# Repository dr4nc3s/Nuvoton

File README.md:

<h1>Nuvoton Main Folder</h1>

Found some Nuvoton MCUs at a 90% discount for a sample sale (max 5pcs/chip) and bought 8 different chips. I need to make breakout/eval boards for them, so I'll use this as an opportunity to learn how to use KiCad (normally use Eagle) and learn developing with uKeil.

<h2> Chips Bought </h2>
1. **M0519SD3AE** - Cortex M0, 64KB Flash, LQFP64_7mmx7mm
	1. UART x2, SPI x2, I2C x1, LIN x2
	2. 16KB RAM, 4KB data flash
	3. Timer x4
	4. PWM x10,
	5. ADC 16-channel, OA x2, Comparator x2

2. **NUC505DS13Y** - Cortex M4, 2048KB Flash, LQFP64
	1. UART x3, USB
	2. I2C x2, I2S x1, SPI x3, SD Host x1
	3. PWM x4, ADC (12-bit) x8
	4. 24-bit Audio CODEC & supports Headphone Out
	5. Digital Mic
	6. RTC, Timer x4
	7. 128KB SRAM
	8. 8KB ISP Loader ROM 

3. **M482SIDAE** - Cortex M4, 512KB Flash, LQFP64_7mmx7mm
	1. UART x6
	2. I2C x3, I2S x1, SPI x4
	3. PWM (16-bit) x24, ADC (12-bit) x16, DAC (12-bit) x2
	4. LIN x2
	5. RTC, Timer x4
	6. 160KB SRAM
	7. 4KB ISP Loader ROM 
	8. LCD Parallel Data Bus, 16-lines

4. **M451VE6AE** - Cortex M4, 128KB Flash, LQFP100
	1. UART x4 + 1 (1 full-duplex)
	2. I2C x2, I2S x2, SPI x3
	3. PWM x12, ADC (12-bit) x16, DAC (12-bit)
	4. LIN x2
	5. RTC, Timer x4
	6. 32KB SRAM
	7. 4KB ISP Loader ROM

5. **M452RE6AE** - Cortex M4, 128KB Flash, LQFP64
	1. UART x4 + 1 (1 full-duplex)
	2. I2C x2, I2S x2, SPI x3
	3. PWM x12, ADC (12-bit) x16, DAC (12-bit)
	4. LIN x2
	5. RTC, Timer x4
	6. 32KB SRAM
	7. 4KB ISP Loader ROM 

6. **NUC505YO13Y** - Cortex M4, 2048KB Flash, QFN88
	1. UART x3, USB
	2. I2C x2, I2S x1, SPI x3, SD Host x1
	3. PWM x4, ADC (12-bit) x8
	4. 24-bit Audio CODEC
	5. Digital Mic
	6. RTC, Timer x4
	7. 128KB SRAM
	8. 8KB ISP Loader ROM

7. **NUC442RI8AE** - Cortex M4, 512KB Flash, LQFP64
	1. UART x4 + 3 (3 full-duplex)
	2. I2C x2, I2S x1, SPI x3
	3. PWM x8, ADC (12-bit) x8, DAC
	4. LIN x4
	5. USB
	6. RTC, Timer x4
	7. 64KB SRAM
	8. 16KB ISP Loader ROM

8. **M451VG6AE** - Cortex M4, 256KB Flash, LQFP100
	1. UART x4 + 1 (1 full-duplex)
	2. I2C x2, I2S x2, SPI x3
	3. PWM x12, ADC (12-bit) x16, DAC (12-bit)
	4. LIN x2
	5. RTC, Timer x4
	6. 32KB SRAM
	7. 4KB ISP Loader ROM

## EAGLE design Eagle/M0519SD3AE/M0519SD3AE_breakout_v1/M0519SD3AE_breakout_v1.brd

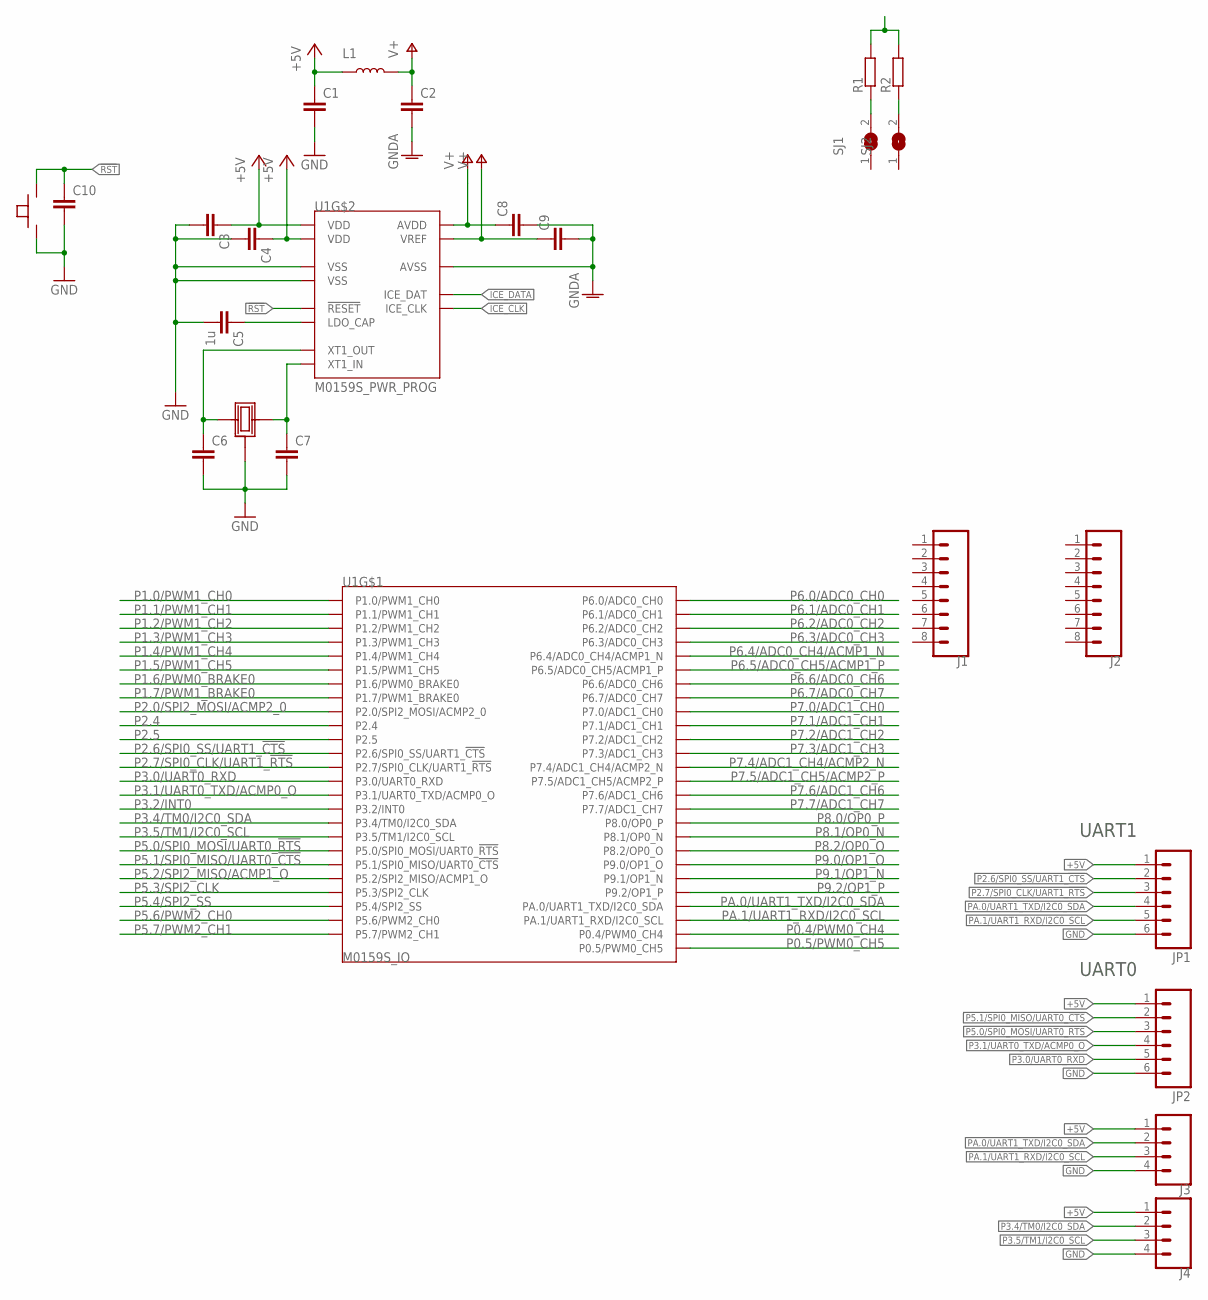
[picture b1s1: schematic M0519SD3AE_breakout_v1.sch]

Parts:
C1, C2, C3, C4, C6, C7, C8, C9, C10: CAP0603-CAP; 0603-CAP
C5: 1u; 0603-CAP
J1, J2: M08; 1X08
J3, J4: M04; 1X04
JP1, JP2: M06LOCK; 1X06_LOCK
L1: INDUCTOR_FB; 0603-FB
R1, R2: RESISTOR0603-RES; 0603-RES
SJ1, SJ2: SJ
U1: M0159S; LQFP-64_7MMX7MMX1.6MM
U$1: CRYSTAL_EPSON; TSX3225
U$2: 95C06B2GWRT; PUSH-BUTTON-95C06B2GWRT

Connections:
!RST: C10.1, U1.60 (!RESET), U$2.P3 (B), U$2.P4 (B)
+5V: C1.1, C3.1, C4.1, J3.1, J4.1, JP1.1, JP2.1, L1.1, U1.6 (VDD), U1.21 (VDD)
GND: C1.2, C3.2, C4.2, C5.2, C6.2, C7.2, C10.2, J3.4, J4.4, JP1.6, JP2.6, U1.7 (VSS), U1.22 (VSS), U$1.2, U$1.4 (2), U$2.P1 (A), U$2.P2 (A)
GNDA: C2.2, C8.2, C9.2, U1.46 (AVSS)
ICE_CLK: U1.64 (ICE_CLK)
ICE_DATA: U1.63 (ICE_DAT)
unnamed: R1.1, SJ1.2
unnamed: C5.1, U1.5 (LDO_CAP)
unnamed: C7.1, U1.62 (XT1_IN), U$1.1
unnamed: C6.1, U1.61 (XT1_OUT), U$1.3
unnamed: R2.1, SJ2.2
unnamed: R1.2, R2.2
P0.4/PWM0_CH4: U1.30 (P0.4/PWM0_CH4)
P0.5/PWM0_CH5: U1.29 (P0.5/PWM0_CH5)
P1.0/PWM1_CH0: U1.18 (P1.0/PWM1_CH0)
P1.1/PWM1_CH1: U1.17 (P1.1/PWM1_CH1)
P1.2/PWM1_CH2: U1.16 (P1.2/PWM1_CH2)
P1.3/PWM1_CH3: U1.15 (P1.3/PWM1_CH3)
P1.4/PWM1_CH4: U1.14 (P1.4/PWM1_CH4)
P1.5/PWM1_CH5: U1.13 (P1.5/PWM1_CH5)
P1.6/PWM0_BRAKE0: U1.12 (P1.6/PWM0_BRAKE0)
P1.7/PWM1_BRAKE0: U1.4 (P1.7/PWM1_BRAKE0)
P2.0/SPI2_MOSI/ACMP2_0: U1.31 (P2.0/SPI2_MOSI/ACMP2_0)
P2.4: U1.28 (P2.4)
P2.5: U1.27 (P2.5)
P2.6/SPI0_SS/UART1_!CTS: JP1.2, U1.26 (P2.6/SPI0_SS/UART1_!CTS)
P2.7/SPI0_CLK/UART1_!RTS: JP1.3, U1.25 (P2.7/SPI0_CLK/UART1_!RTS)
P3.0/UART0_RXD: JP2.5, U1.19 (P3.0/UART0_RXD)
P3.1/UART0_TXD/ACMP0_O: JP2.4, U1.20 (P3.1/UART0_TXD/ACMP0_O)
P3.2/INT0: U1.3 (P3.2/INT0)
P3.4/TM0/I2C0_SDA: J4.2, U1.2 (P3.4/TM0/I2C0_SDA)
P3.5/TM1/I2C0_SCL: J4.3, U1.1 (P3.5/TM1/I2C0_SCL)
P5.0/SPI0_MOSI/UART0_!RTS: JP2.3, U1.23 (P5.0/SPI0_MOSI/UART0_!RTS)
P5.1/SPI0_MISO/UART0_!CTS: JP2.2, U1.24 (P5.1/SPI0_MISO/UART0_!CTS)
P5.2/SPI2_MISO/ACMP1_O: U1.32 (P5.2/SPI2_MISO/ACMP1_O)
P5.3/SPI2_CLK: U1.33 (P5.3/SPI2_CLK)
P5.4/SPI2_SS: U1.34 (P5.4/SPI2_SS)
P5.6/PWM2_CH0: U1.11 (P5.6/PWM2_CH0)
P5.7/PWM2_CH1: U1.10 (P5.7/PWM2_CH1)
P6.0/ADC0_CH0: U1.42 (P6.0/ADC0_CH0)
P6.1/ADC0_CH1: U1.41 (P6.1/ADC0_CH1)
P6.2/ADC0_CH2: U1.40 (P6.2/ADC0_CH2)
P6.3/ADC0_CH3: U1.39 (P6.3/ADC0_CH3)
P6.4/ADC0_CH4/ACMP1_N: U1.38 (P6.4/ADC0_CH4/ACMP1_N)
P6.5/ADC0_CH5/ACMP1_P: U1.37 (P6.5/ADC0_CH5/ACMP1_P)
P6.6/ADC0_CH6: U1.36 (P6.6/ADC0_CH6)
P6.7/ADC0_CH7: U1.35 (P6.7/ADC0_CH7)
P7.0/ADC1_CH0: U1.56 (P7.0/ADC1_CH0)
P7.1/ADC1_CH1: U1.55 (P7.1/ADC1_CH1)
P7.2/ADC1_CH2: U1.54 (P7.2/ADC1_CH2)
P7.3/ADC1_CH3: U1.53 (P7.3/ADC1_CH3)
P7.4/ADC1_CH4/ACMP2_N: U1.52 (P7.4/ADC1_CH4/ACMP2_N)
P7.5/ADC1_CH5/ACMP2_P: U1.51 (P7.5/ADC1_CH5/ACMP2_P)
P7.6/ADC1_CH6: U1.50 (P7.6/ADC1_CH6)
P7.7/ADC1_CH7: U1.49 (P7.7/ADC1_CH7)
P8.0/OP0_P: U1.45 (P8.0/OP0_P)
P8.1/OP0_N: U1.44 (P8.1/OP0_N)
P8.2/OP0_O: U1.43 (P8.2/OP0_O)
P9.0/OP1_O: U1.57 (P9.0/OP1_O)
P9.1/OP1_N: U1.58 (P9.1/OP1_N)
P9.2/OP1_P: U1.59 (P9.2/OP1_P)
PA.0/UART1_TXD/I2C0_SDA: J3.2, JP1.4, U1.9 (PA.0/UART1_TXD/I2C0_SDA)
PA.1/UART1_RXD/I2C0_SCL: J3.3, JP1.5, U1.8 (PA.1/UART1_RXD/I2C0_SCL)
V+: C2.1, C8.1, C9.1, L1.2, U1.47 (AVDD), U1.48 (VREF)

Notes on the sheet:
UART1
UART0

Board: 2 copper layers, 24 parts (0 on the bottom side), 21 nets, no tracks yet.

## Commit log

2018-09-30 :neckbeard: Added .gitattributes & .gitignore files
2018-09-30 Added README
2018-09-30 Added datasheets
2018-09-30 Edited README
2018-10-01 Started Nuvoton kicad library
2018-10-01 Added MCU
2018-10-02 Gave up, switch back to Eagle
2018-10-02 Made M0519S device in library
2018-10-02 power portion done
2019-02-02 made some
